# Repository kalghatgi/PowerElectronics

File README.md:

View this project on [CADLAB.io](https://cadlab.io/project/28492). 

# PowerElectronics

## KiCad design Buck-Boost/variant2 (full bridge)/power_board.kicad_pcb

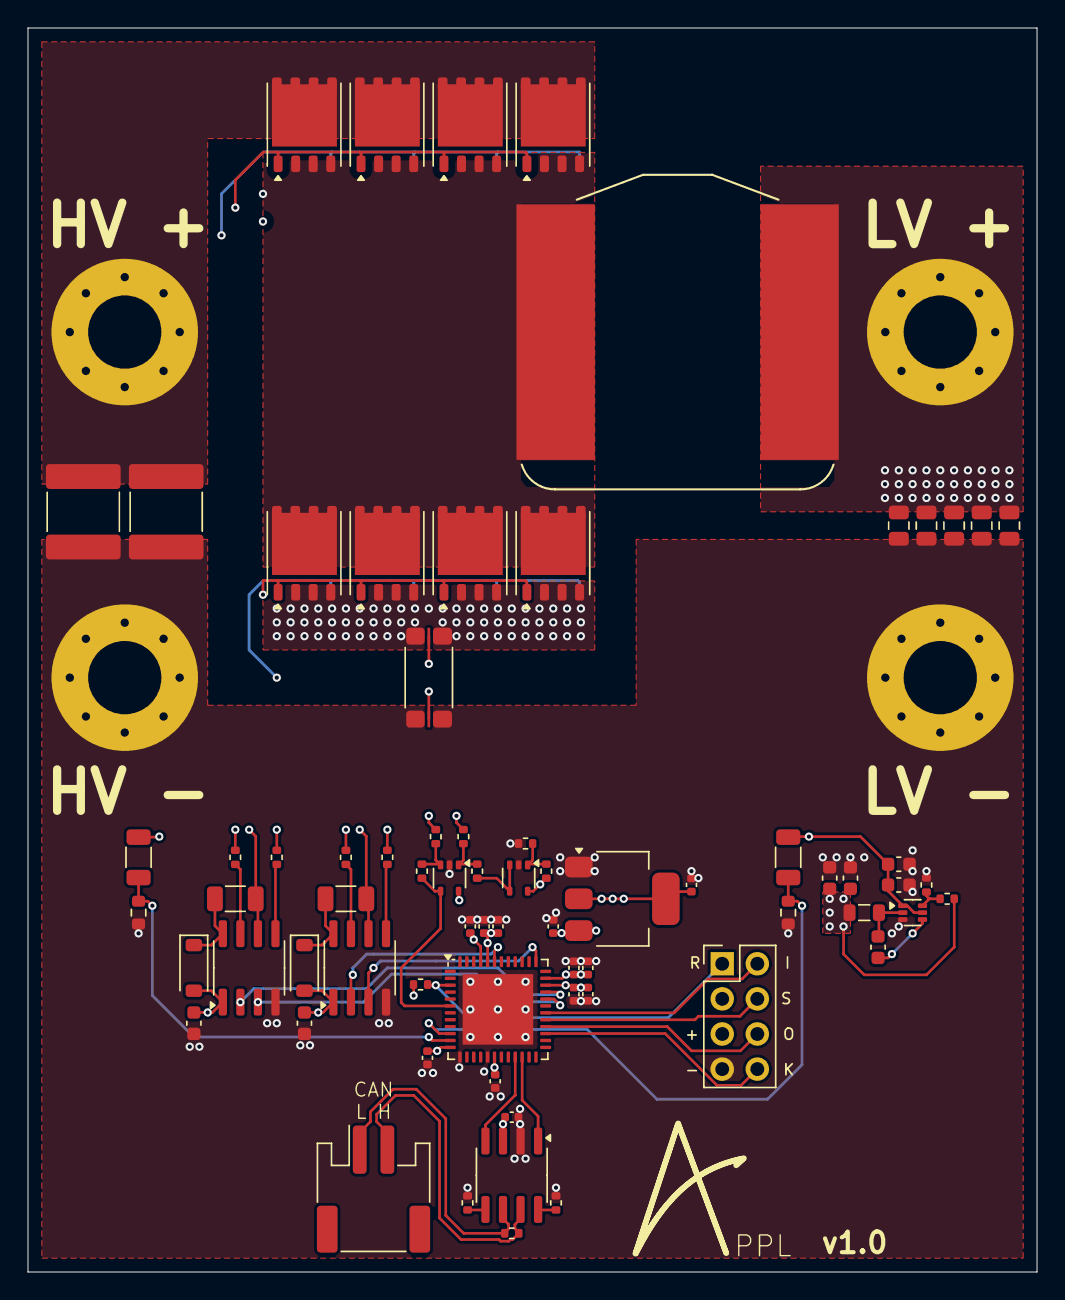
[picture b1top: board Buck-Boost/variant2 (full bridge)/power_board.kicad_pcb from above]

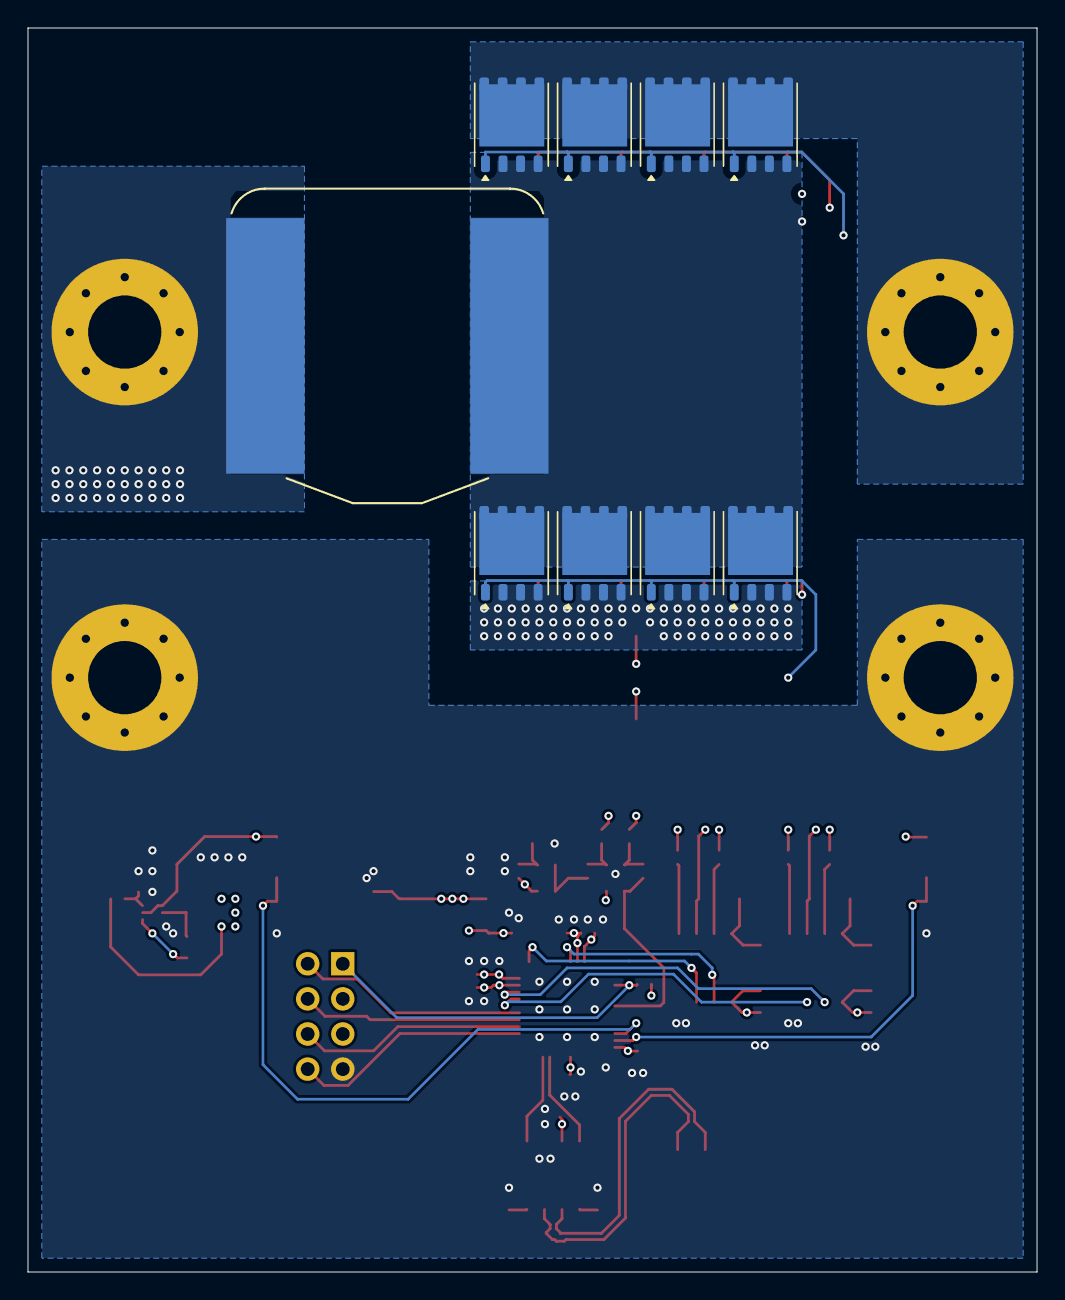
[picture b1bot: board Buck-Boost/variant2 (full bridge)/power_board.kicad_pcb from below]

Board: 4 copper layers, 73.0 x 90.0 mm, 84 parts (9 on the bottom side), 45 nets.

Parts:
C1, C2: 22uF, >=120V; C_2220_5750Metric
C3, C4, C5, C6, C7: >22uF, >25V; C_0805_2012Metric
C8, C31, C33: 10uF, >=25V; C_0603_1608Metric
C10, C13: 100nF, >=25V; C_0603_1608Metric
C12, C14, C26, C27, C28, C29, C30: 1uF, >=6.3V; C_0402_1005Metric
C18, C21: 22uF, >=6.3V; C_0603_1608Metric
C19, C25: 10uF, >=6.3V; C_0402_1005Metric
C22, C24: 100nF, >=6.3V; C_0402_1005Metric
C23: 4.7uF, >=6.3V; C_0402_1005Metric
C32, C34: 100nF, >=25V; C_1206_3216Metric
D3, D4: Vr>=600V, If>=1A; D_SOD-123
H1, H2, H3, H4: MountingHole_Pad; MountingHole_5.3mm_M5_Pad_Via
IC1: F2800137RGZR; QFN-48-1EP_7x7mm_P0.5mm_EP5.1x5.1mm
J1: Conn_01x02_Pin; JST_PH_S2B-PH-SM4-TB_1x02-1MP_P2.00mm_Horizontal
J3: Conn_02x04_Counter_Clockwise; PinHeader_2x04_P2.54mm_Vertical
L1, L2: 15uH, IRMS>100A, Isat>175A; IND_MPX1D2213L680_KEM
L4: 3.3uH, >=0.5A; L_0805_2012Metric
Q1, Q2, Q3, Q4, Q5, Q6, Q7, Q8, Q9, Q10, Q11, Q12, Q13, Q14, Q15, Q16: NMOS, Vds>=80V, Rds<=1.5mOhm; Infineon_PG-TDSON-8_6.15x5.15mm
R1, R4: 1MOhm, >200V, <1%, >62.5mW; R_1206_3216Metric
R2, R5: 10K, >62.5mW; R_0603_1608Metric
R3: 500uOhm, >=3W; R_shunt_2512_6332Metric
R6, R7, R8, R9, R13, R14, R17, R18, R27: 10K, 62.5mW, 0402; R_0402_1005Metric
R15, R16, R28, R29: 4R, 62.5mW, 0402; R_0402_1005Metric
R21: 120R, 62.5mW, 0402; R_0402_1005Metric
R22: 30.9K, >62.5mW, 0402; R_0402_1005Metric
R23: 10K, >62.5mW, 0402; R_0402_1005Metric
U1, U5: LMV321; SOT-353_SC-70-5
U2: TCAN3414DR; SOIC-8_3.9x4.9mm_P1.27mm
U3: TPS562202; SOT-563
U4: LD1117S12TR_SOT223; SOT-223-3_TabPin2
U6, U7: IR2101; SOIC-8_3.9x4.9mm_P1.27mm

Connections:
+1.2V: C19.1, C22.1, C23.1, C24.1, C25.1, IC1.35 (VDD), IC1.44 (VDD), U4.2 (VO)
+3.3V: C12.1, C14.1, C18.1, C21.1, C26.1, C27.1, C28.1, C29.1, C30.1, IC1.12 (VREFHI), IC1.18 (VDDA), IC1.34 (VDDIO), IC1.45 (VDDIO), J3.5, L4.1, R6.1, R22.1, R27.1, U1.5 (V+), U2.3 (VCC), U4.3 (VI), U5.5 (V+)
+12V: C3.1, C4.1, C5.1, C6.1, C7.1, C8.1, C10.1, C31.1, C33.1, D3.2 (A), D4.2 (A), H1.1, L1.1, L2.1, R4.1, U3.1 (VIN), U3.5 (EN), U6.1 (VCC), U7.1 (VCC)
/CAN_N: J1.1, R21.2, U2.6 (CANL)
/CAN_P: J1.2, R21.1, U2.7 (CANH)
/CAN_Rx: IC1.21 (A10/C10/GPIO230), U2.4 (RXD)
/CAN_Tx: IC1.22 (A19/C19/GPIO13), U2.1 (TXD)
/HG_A: Q9.1 (G), Q11.1 (G), Q13.1 (G), Q15.1 (G), R28.1
/HG_B: Q1.1 (G), Q3.1 (G), Q5.1 (G), Q7.1 (G), R15.1
/HS_A: C32.2, L1.2, Q9.2 (S), Q9.3 (S), Q9.4 (S), Q10.5 (D), Q11.2 (S), Q11.3 (S), Q11.4 (S), Q12.5 (D), Q13.2 (S), Q13.3 (S), Q13.4 (S), Q14.5 (D), Q15.2 (S), Q15.3 (S), Q15.4 (S), Q16.5 (D), U7.6 (VS)
/HS_B: C34.2, L2.2, Q1.2 (S), Q1.3 (S), Q1.4 (S), Q2.5 (D), Q3.2 (S), Q3.3 (S), Q3.4 (S), Q4.5 (D), Q5.2 (S), Q5.3 (S), Q5.4 (S), Q6.5 (D), Q7.2 (S), Q7.3 (S), Q7.4 (S), Q8.5 (D), U6.6 (VS)
/HV+: C1.1, C2.1, H4.1, Q1.5 (D), Q3.5 (D), Q5.5 (D), Q7.5 (D), Q9.5 (D), Q11.5 (D), Q13.5 (D), Q15.5 (D), R1.1
/I: IC1.6 (A2/C9/GPIO224), R18.1, U5.4
/I+: R3.3, R13.2
/I-: R3.2, R14.2
/LG_A: Q10.1 (G), Q12.1 (G), Q14.1 (G), Q16.1 (G), R29.1
/LG_B: Q2.1 (G), Q4.1 (G), Q6.1 (G), Q8.1 (G), R16.1
/PWM_H_A: IC1.43 (GPIO7), U7.2 (HIN)
/PWM_H_B: IC1.33 (GPIO19X1), U6.2 (HIN)
/PWM_L_A: IC1.37 (GPIO4), U7.3 (LIN)
/PWM_L_B: IC1.32 (GPIO18X2), U6.3 (LIN)
/TCK: IC1.27 (TCK), J3.8
/TDI: IC1.30 (GPIO35/TDI), J3.2
/TDO: IC1.28 (GPIO37/TDO), J3.6
/TMS: IC1.29 (TMS), J3.4
/V_hv: IC1.11 (A0/C15/CMP1_DACL), R1.2, R2.1
/V_lv: IC1.10 (A1), R4.2, R5.1
/~RST: IC1.3 (XRSN), J3.1, R27.2
GND0: C1.2, C2.2, C3.2, C4.2, C5.2, C6.2, C7.2, C8.2, C10.2, C12.2, C14.2, C18.2, C19.2, C21.2, C22.2, C23.2, C24.2, C25.2, C26.2, C27.2, C28.2, C29.2, C30.2, C31.2, C33.2, H2.1, H3.1, IC1.13 (VREFLO), IC1.17 (VSSA), IC1.49 (VSS), J3.7, R2.2, R3.4, R5.2, R7.2, R8.2, R9.2, R23.2, U1.2 (V-), U2.2 (GND), U3.3 (GND), U4.1 (GND), U5.2 (V-), U6.4 (COM), U7.4 (COM)
unnamed: C32.1, D3.1 (K), U7.8 (VB)
unnamed: C34.1, D4.1 (K), U6.8 (VB)
unnamed: Q2.2 (S), Q2.3 (S), Q2.4 (S), Q4.2 (S), Q4.3 (S), Q4.4 (S), Q6.2 (S), Q6.3 (S), Q6.4 (S), Q8.2 (S), Q8.3 (S), Q8.4 (S), Q10.2 (S), Q10.3 (S), Q10.4 (S), Q12.2 (S), Q12.3 (S), Q12.4 (S), Q14.2 (S), Q14.3 (S), Q14.4 (S), Q16.2 (S), Q16.3 (S), Q16.4 (S), R3.1
unnamed: R6.2, R7.1, U1.1 (+)
unnamed: R17.2, U1.3 (-), U1.4
unnamed: R8.1, U2.5 (SHDN)
unnamed: R9.1, U2.8 (STB)
unnamed: C13.1, L4.2, U3.2 (SW)
unnamed: C13.2, U3.4 (VBST)
unnamed: R22.2, R23.1, U3.6 (VFB)
unnamed: R13.1, R17.1, U5.1 (+)
unnamed: R14.1, R18.2, U5.3 (-)
unnamed: R15.2, U6.7 (HO)
unnamed: R16.2, U6.5 (LO)
unnamed: R28.2, U7.7 (HO)
unnamed: R29.2, U7.5 (LO)

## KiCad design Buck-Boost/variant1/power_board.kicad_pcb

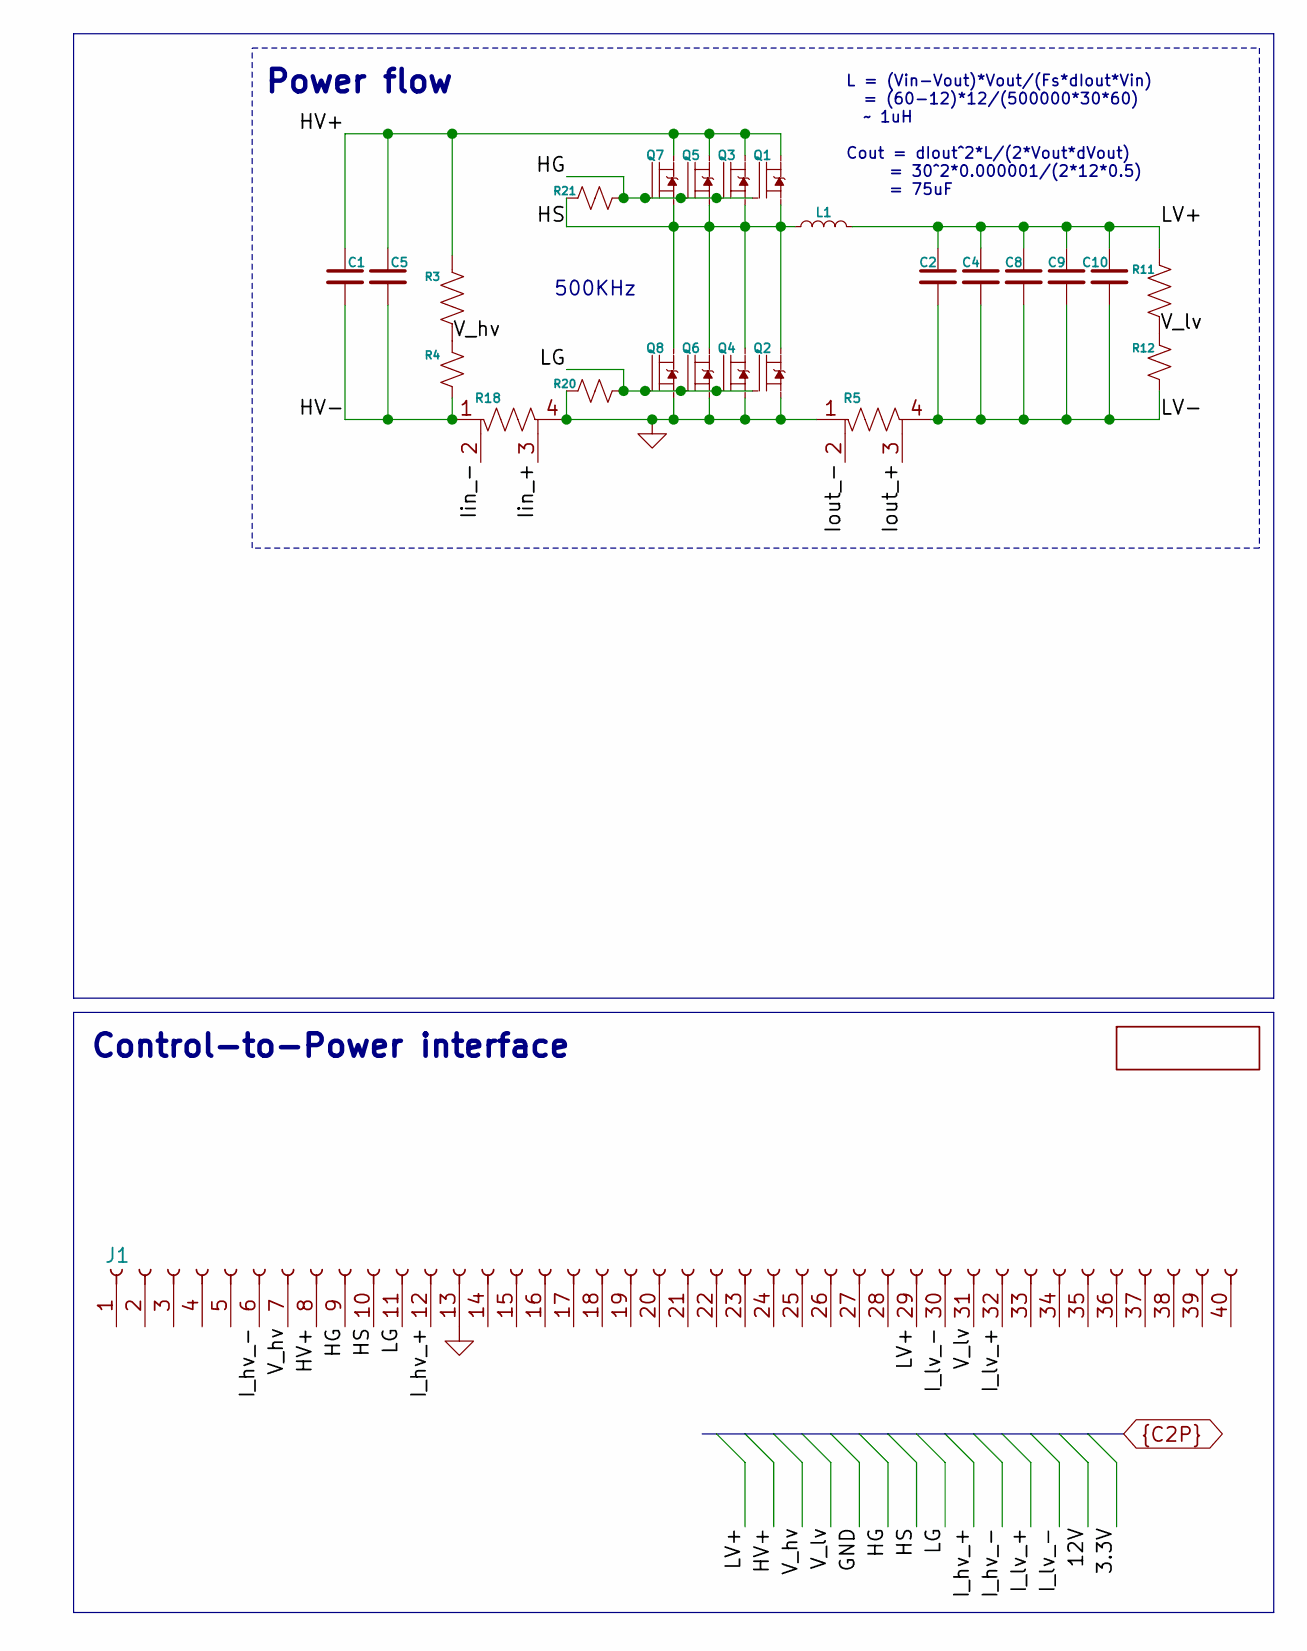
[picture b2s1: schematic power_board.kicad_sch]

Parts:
C1, C5: 22uF, >=120V; C_2220_5750Metric
C2, C4, C8, C9, C10: >22uF, >25V; C_0805_2012Metric
J1: Conn_01x05_Header; PinHeader_1x40_P2.54mm_Vertical_SMD_Pin1Left
L1: 15uH, IRMS>100A, Isat>175A; IND_MPX1D2213L680_KEM; MPN MPX1D2213L1R0
Q1, Q2, Q3, Q4, Q5, Q6, Q7, Q8: NMOS, Vds>=80V, Rds<=1.5mOhm; Infineon_PG-TDSON-8_6.15x5.15mm; MPN IAUCN04S7N005ATMA1
R3, R11: 1MOhm, >200V, <1%, >62.5mW; R_1206_3216Metric
R4, R12: 10K, >62.5mW; R_0603_1608Metric
R5, R18: 500uOhm, >=3W; R_shunt_2512_6332Metric
R20, R21: 10K, >62.5mW, 0402; R_0402_1005Metric

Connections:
/HV-: C1.2, C5.2, R4.2, R18.1
/Iin_+: R18.3
/Iin_-: R18.2
/Iout_+: R5.3
/Iout_-: R5.2
/LV-: C2.2, C4.2, C8.2, C9.2, C10.2, R5.4, R12.2
GND0: J1.13, Q2.2 (S), Q2.3 (S), Q2.4 (S), Q4.2 (S), Q4.3 (S), Q4.4 (S), Q6.2 (S), Q6.3 (S), Q6.4 (S), Q8.2 (S), Q8.3 (S), Q8.4 (S), R5.1, R18.4, R20.2
HG: J1.9, Q1.1 (G), Q3.1 (G), Q5.1 (G), Q7.1 (G), R21.1
HS: J1.10, L1.2, Q1.2 (S), Q1.3 (S), Q1.4 (S), Q2.5 (D), Q3.2 (S), Q3.3 (S), Q3.4 (S), Q4.5 (D), Q5.2 (S), Q5.3 (S), Q5.4 (S), Q6.5 (D), Q7.2 (S), Q7.3 (S), Q7.4 (S), Q8.5 (D), R21.2
HV+: C1.1, C5.1, J1.8, Q1.5 (D), Q3.5 (D), Q5.5 (D), Q7.5 (D), R3.1
I_hv_+: J1.12
I_hv_-: J1.6
I_lv_+: J1.32
I_lv_-: J1.30
LG: J1.11, Q2.1 (G), Q4.1 (G), Q6.1 (G), Q8.1 (G), R20.1
LV+: C2.1, C4.1, C8.1, C9.1, C10.1, J1.29, L1.1, R11.1
V_hv: J1.7, R3.2, R4.1
V_lv: J1.31, R11.2, R12.1

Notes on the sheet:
500KHz
Power flow
Control-to-Power interface
L = (Vin-Vout)*Vout/(Fs*dIout*Vin) = (60-12)*12/(500000*30*60) ~ 1uH Cout = dIout^2*L/(2*Vout*dVout) = 30^2*0.000001/(2*12*0.5) = 75uF

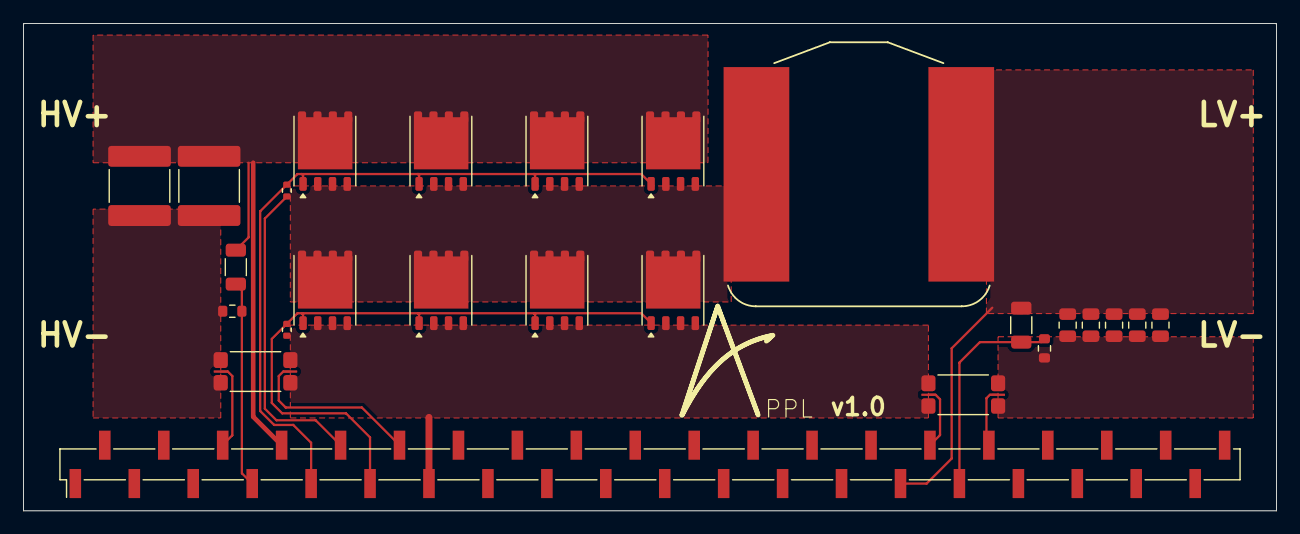
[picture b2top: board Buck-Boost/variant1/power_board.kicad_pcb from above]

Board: 2 copper layers, 108.0 x 42.0 mm, 25 parts (0 on the bottom side), 10 nets.

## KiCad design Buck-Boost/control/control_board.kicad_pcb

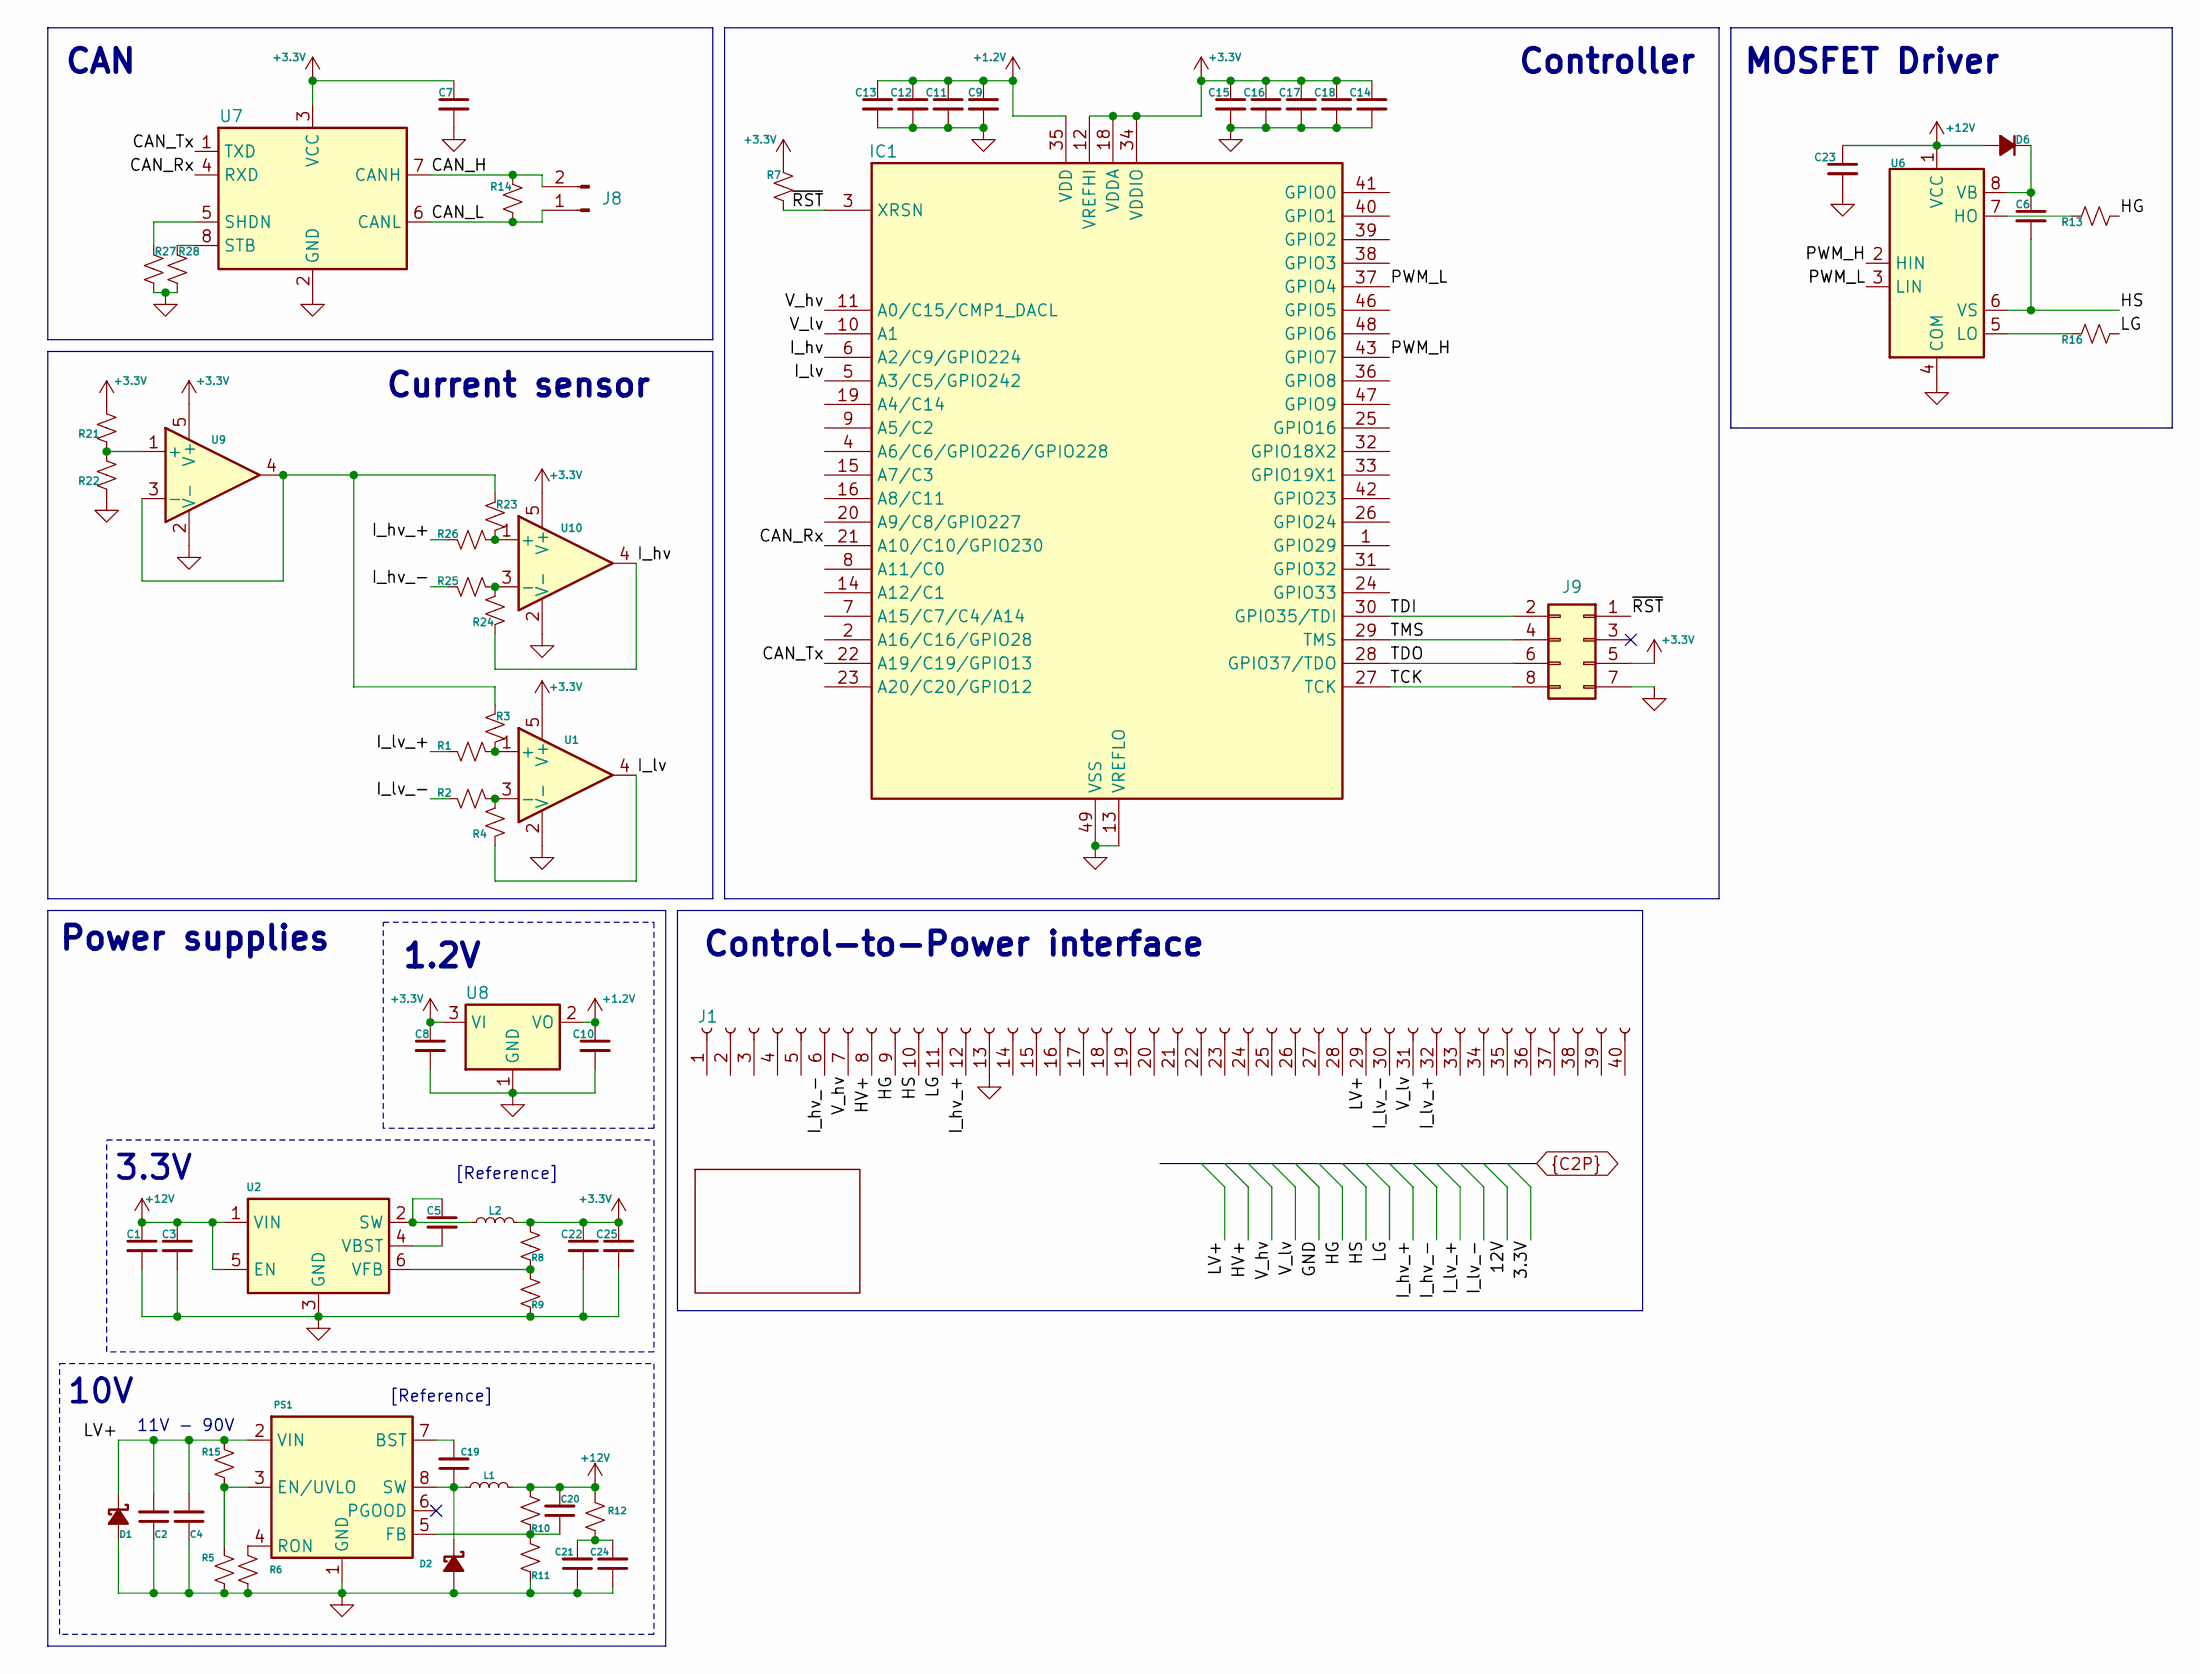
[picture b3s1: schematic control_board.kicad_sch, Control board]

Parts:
C1, C23: 10uF, >=25V; C_0603_1608Metric
C2, C4: 2.2uF, >=100V, 1206; C_1210_3225Metric; MPN mcmt32b225k101ct
C3, C5: 100nF, >=25V; C_0603_1608Metric
C6: 100nF, >=25V; C_1206_3216Metric
C7, C8, C14, C15, C16, C17, C18: 1uF, >=6.3V; C_0402_1005Metric
C9, C10: 10uF, >=6.3V; C_0402_1005Metric
C11, C13: 100nF, >=6.3V; C_0402_1005Metric
C12: 4.7uF, >=6.3V; C_0402_1005Metric
C19: 2200pF, >=25V, 0603; C_0603_1608Metric; MPN mc0805b222k500ct
C20: 100pF, >=25V, 0402; C_0402_1005Metric; MPN mc0402b101k500ct
C21, C24: 22uF, >=25V, 0603; C_0603_1608Metric; MPN grm21br61e226me44k
C22, C25: 22uF, >=6.3V; C_0603_1608Metric
D1: Vs=110V Vb=120V SOD-123; D_SOD-123F; MPN pmeg120g10elrx
D2: Vr=100V Vf=0.6V If=2.5A; D_SMP_DO-220AA; MPN v3pm10-m3-h
D6: Vr>=600V, If>=1A; D_SOD-123
IC1: F2800137RGZR; QFN-48-1EP_7x7mm_P0.5mm_EP5.1x5.1mm
J1: Conn_01x05_Header; PinSocket_1x40_P2.54mm_Horizontal
J8: Conn_01x02_Pin; JST_PH_S2B-PH-SM4-TB_1x02-1MP_P2.00mm_Horizontal
J9: Conn_02x04_Counter_Clockwise; PinHeader_2x04_P2.54mm_Vertical
L1: 150uH, <=900mOhm; L_Taiyo-Yuden_MD-4040; MPN 74404054151
L2: 3.3uH, >=0.5A; L_0805_2012Metric; MPN LQM21PN3R3NGRD
PS1: Vin>=90V, Iout>=2.0A; SOIC-8-1EP_3.9x4.9mm_P1.27mm_EP2.29x3mm_ThermalVias; MPN LM5012DDAR
R1, R2, R3, R4, R7, R21, R22, R23, R24, R25, R26, R27, R28: 10K, 62.5mW, 0402; R_0402_1005Metric
R5: 16.9K, >=62.5mW, 0402; R_0402_1005Metric
R6: 59K, >=62.5mW, 0402; R_0402_1005Metric; MPN mcwr04x5902ftl
R8: 30.9K, >62.5mW, 0402; R_0402_1005Metric
R9: 10K, >62.5mW, 0402; R_0402_1005Metric
R10: 732K, >=62.5mW, 0402; R_0402_1005Metric
R11: 101K, >=62.5mW, 0402; R_0402_1005Metric
R12: 0.560R, 62.5mW, 0402; R_0402_1005Metric; MPN rl0402fr-070r5l
R13, R16: 4R, 62.5mW, 0402; R_0402_1005Metric
R14: 120R, 62.5mW, 0402; R_0402_1005Metric
R15: 100K, >=62.5mW, 0402; R_0805_2012Metric
U1, U9, U10: LMV321; SOT-353_SC-70-5
U2: TPS562202; SOT-563
U6: IR2101; SOIC-8_3.9x4.9mm_P1.27mm
U7: TCAN3414DR; SOIC-8_3.9x4.9mm_P1.27mm
U8: LD1117S12TR_SOT223; SOT-223-3_TabPin2

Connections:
+1.2V: C9.1, C10.1, C11.1, C12.1, C13.1, IC1.35 (VDD), IC1.44 (VDD), U8.2 (VO)
+3.3V: C7.1, C8.1, C14.1, C15.1, C16.1, C17.1, C18.1, C22.1, C25.1, IC1.12 (VREFHI), IC1.18 (VDDA), IC1.34 (VDDIO), IC1.45 (VDDIO), J9.5, L2.1, R7.1, R8.1, R21.1, U1.5 (V+), U7.3 (VCC), U8.3 (VI), U9.5 (V+), U10.5 (V+)
+12V: C1.1, C3.1, C20.2, C23.1, D6.2 (A), L1.2, R10.1, R12.1, U2.1 (VIN), U2.5 (EN), U6.1 (VCC)
/CAN_H: J8.2, R14.1, U7.7 (CANH)
/CAN_L: J8.1, R14.2, U7.6 (CANL)
/CAN_Rx: IC1.21 (A10/C10/GPIO230), U7.4 (RXD)
/CAN_Tx: IC1.22 (A19/C19/GPIO13), U7.1 (TXD)
/I_hv: IC1.6 (A2/C9/GPIO224), R24.1, U10.4
/I_lv: IC1.5 (A3/C5/GPIO242), R4.1, U1.4
/PWM_H: IC1.43 (GPIO7), U6.2 (HIN)
/PWM_L: IC1.37 (GPIO4), U6.3 (LIN)
/TCK: IC1.27 (TCK), J9.8
/TDI: IC1.30 (GPIO35/TDI), J9.2
/TDO: IC1.28 (GPIO37/TDO), J9.6
/TMS: IC1.29 (TMS), J9.4
/~RST: IC1.3 (XRSN), J9.1, R7.2
GND0: C1.2, C2.1, C3.2, C4.1, C7.2, C8.2, C9.2, C10.2, C11.2, C12.2, C13.2, C14.2, C15.2, C16.2, C17.2, C18.2, C21.1, C22.2, C23.2, C24.1, C25.2, D1.2 (A), D2.2 (A), IC1.13 (VREFLO), IC1.17 (VSSA), IC1.49 (VSS), J1.13, J9.7, PS1.1 (GND), PS1.9 (GND_thermal), R5.2, R6.1, R9.2, R11.2, R22.2, R27.2, R28.2, U1.2 (V-), U2.3 (GND), U6.4 (COM), U7.2 (GND), U8.1 (GND), U9.2 (V-), U10.2 (V-)
HG: J1.9, R13.1
HS: C6.2, J1.10, U6.6 (VS)
HV+: J1.8
I_hv_+: J1.12, R26.2
I_hv_-: J1.6, R25.2
I_lv_+: J1.32, R1.2
I_lv_-: J1.30, R2.2
LG: J1.11, R16.1
LV+: C2.2, C4.2, D1.1 (K), J1.29, PS1.2 (VIN), R15.1
unnamed: C21.2, C24.2, R12.2
unnamed: C19.1, D2.1 (K), L1.1, PS1.8 (SW)
unnamed: C6.1, D6.1 (K), U6.8 (VB)
unnamed: C19.2, PS1.7 (BST)
unnamed: PS1.3 (EN/UVLO), R5.1, R15.2
unnamed: C20.1, PS1.5 (FB), R10.2, R11.1
unnamed: PS1.4 (RON), R6.2
unnamed: R1.1, R3.1, U1.1 (+)
unnamed: R2.1, R4.2, U1.3 (-)
unnamed: C5.1, L2.2, U2.2 (SW)
unnamed: C5.2, U2.4 (VBST)
unnamed: R8.2, R9.1, U2.6 (VFB)
unnamed: R13.2, U6.7 (HO)
unnamed: R16.2, U6.5 (LO)
unnamed: R27.1, U7.5 (SHDN)
unnamed: R28.1, U7.8 (STB)
unnamed: R21.2, R22.1, U9.1 (+)
unnamed: R3.2, R23.2, U9.3 (-), U9.4
unnamed: R23.1, R26.1, U10.1 (+)
unnamed: R24.2, R25.1, U10.3 (-)
V_hv: IC1.11 (A0/C15/CMP1_DACL), J1.7
V_lv: IC1.10 (A1), J1.31

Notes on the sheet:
11V - 90V
[Reference]
Control-to-Power interface
10V
Controller
MOSFET Driver
CAN
1.2V
Power supplies
3.3V
Current sensor

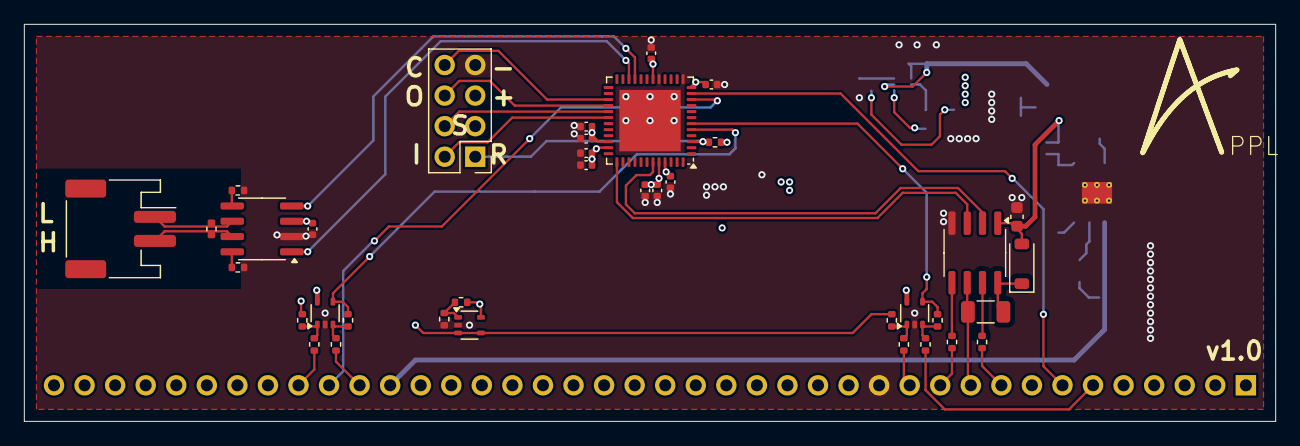
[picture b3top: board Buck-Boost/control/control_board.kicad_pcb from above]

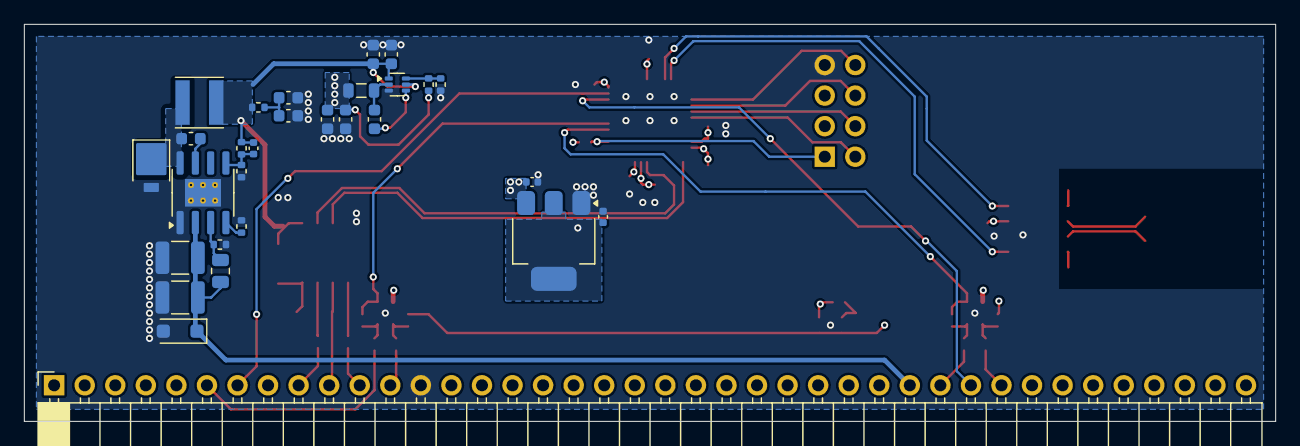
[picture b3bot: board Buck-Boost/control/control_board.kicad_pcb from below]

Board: 4 copper layers, 104.0 x 33.0 mm, 66 parts (29 on the bottom side), 47 nets.

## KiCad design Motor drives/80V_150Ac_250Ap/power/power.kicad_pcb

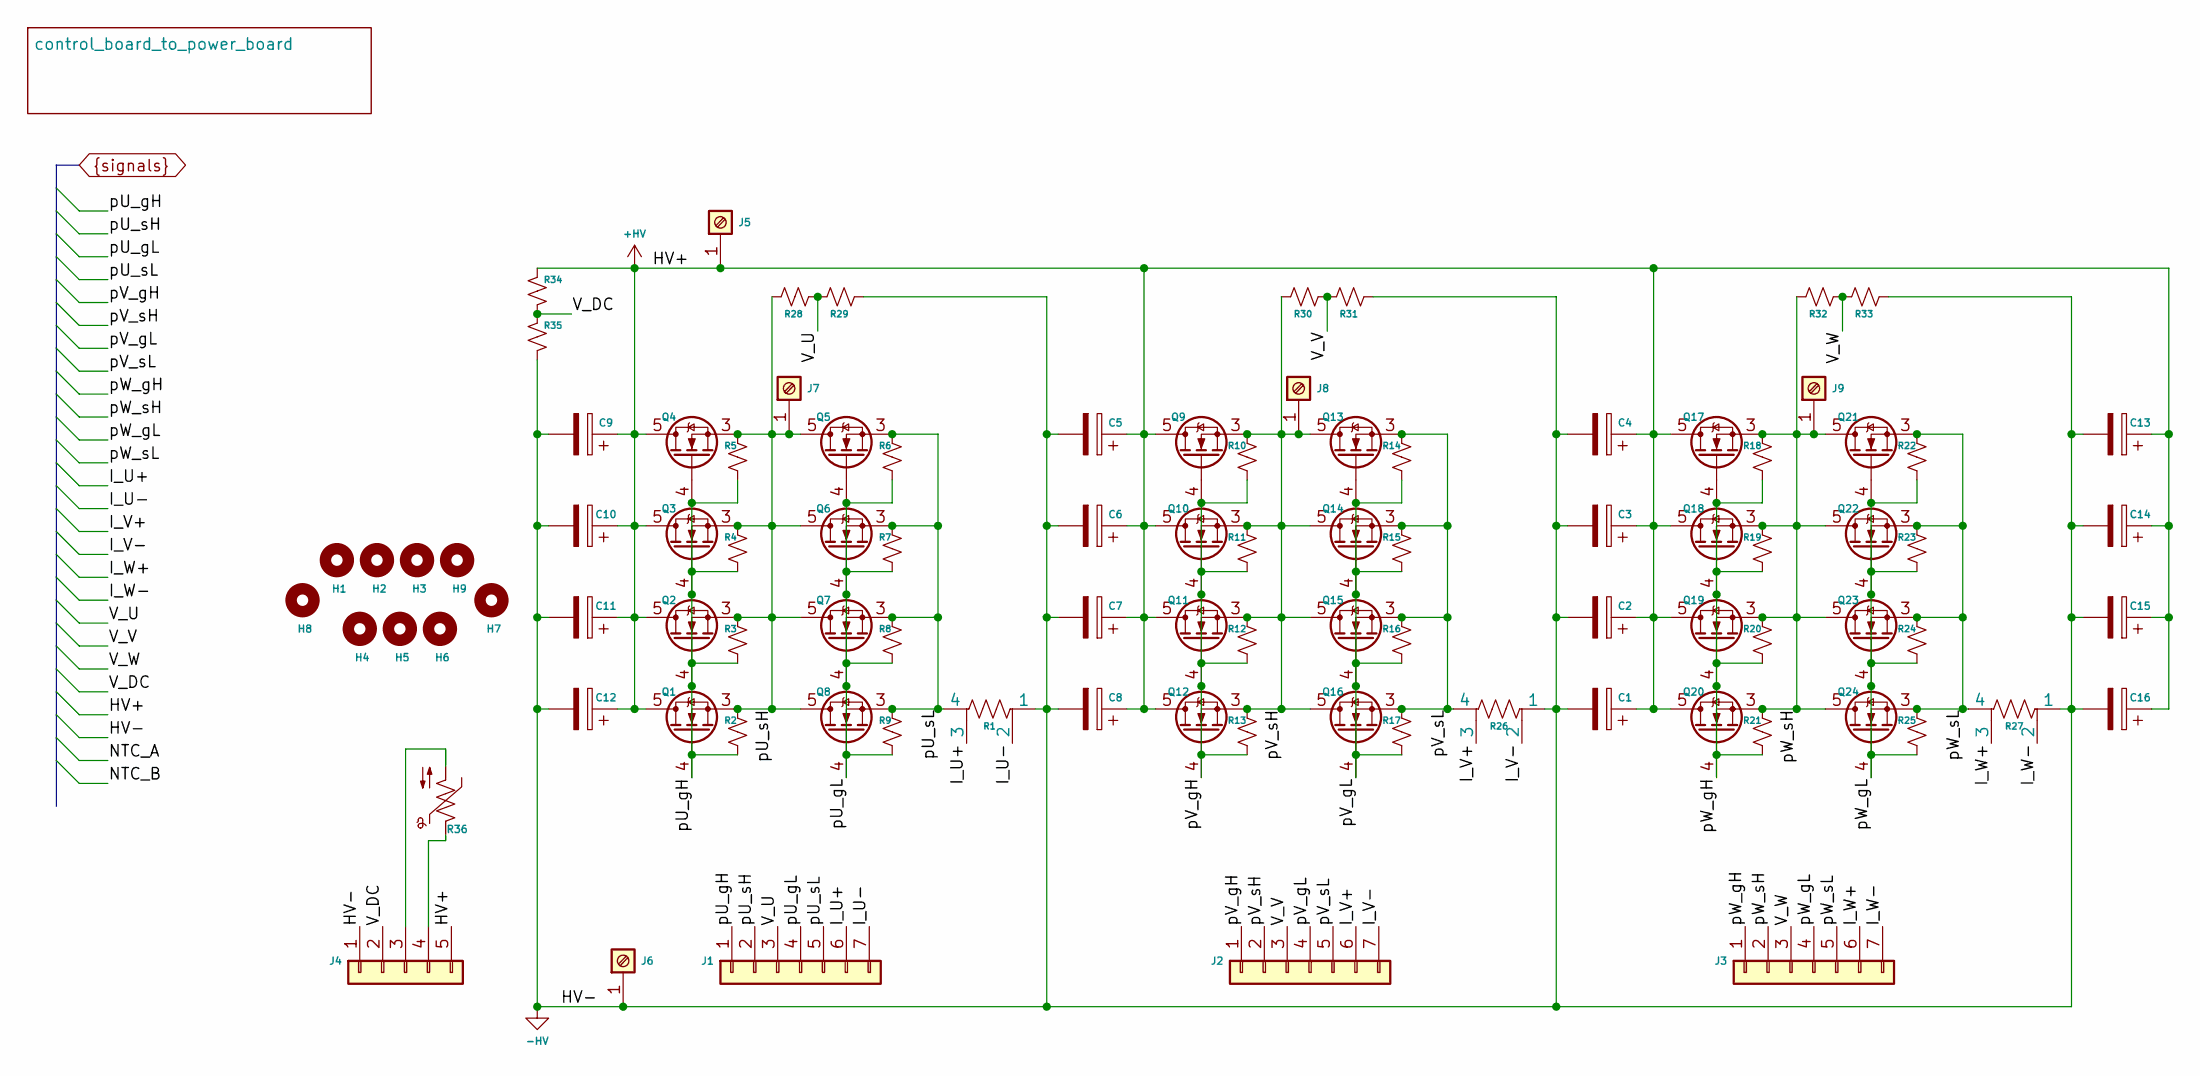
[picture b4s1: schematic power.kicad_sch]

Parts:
C1, C2, C3, C4, C5, C6, C7, C8, C9, C10, C11, C12, C13, C14, C15, C16: 220uF, >=120V; CP_Elec_18x17.5
H1, H2, H3, H4, H5, H6, H7, H8, H9: M3, no pads; M3 x 6mm brass threaded hex spacer
J1, J2, J3: Conn_01x07; PinSocket_1x07_P2.54mm_Vertical_SMD_Pin1Left
J4: Conn_01x05; PinSocket_1x05_P2.54mm_Vertical_SMD_Pin1Left
J5, J6, J7, J8, J9: M8 lug; terminal_lug
Q1, Q2, Q3, Q4, Q5, Q6, Q7, Q8, Q9, Q10, Q11, Q12, Q13, Q14, Q15, Q16, Q17, Q18, Q19, Q20, Q21, Q22, Q23, Q24: NMOS, >80V, <1.5mOhm; IAUCN08S7N013ATMA1; MPN IAUCN08S7N013ATMA1
R1, R26, R27: 100uOhms, 15W; RES_Y14860R00010F9R_VIS_1; MPN Y14860R00010F9R
R2, R3, R4, R5, R6, R7, R8, R9, R10, R11, R12, R13, R14, R15, R16, R17, R18, R19, R20, R21, R22, R23, R24, R25, R29, R31, R33, R35: 10K, >=62.5mW, 0402; R_0402_1005Metric; MPN mcwr04x1002ftl
R28, R30, R32, R34: 220K, >=62.5mW, 0805; R_0805_2012Metric
R36: 10K NTC; R_0603_1608Metric; MPN tx06f103f3435er

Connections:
+HV: C1.1, C2.1, C3.1, C4.1, C5.1, C6.1, C7.1, C8.1, C9.1, C10.1, C11.1, C12.1, C13.1, C14.1, C15.1, C16.1, J4.5, J5.1, Q1.5 (D), Q2.5 (D), Q3.5 (D), Q4.5 (D), Q9.5 (D), Q10.5 (D), Q11.5 (D), Q12.5 (D), Q17.5 (D), Q18.5 (D), Q19.5 (D), Q20.5 (D), R34.2
-HV: C1.2, C2.2, C3.2, C4.2, C5.2, C6.2, C7.2, C8.2, C9.2, C10.2, C11.2, C12.2, C13.2, C14.2, C15.2, C16.2, J4.1, J6.1, R1.1, R26.1, R27.1, R29.1, R31.1, R33.1, R35.1
I_U+: J1.6, R1.3
I_U-: J1.7, R1.2
I_V+: J2.6, R26.3
I_V-: J2.7, R26.2
I_W+: J3.6, R27.3
I_W-: J3.7, R27.2
unnamed: J4.3, R36.2
unnamed: J4.4, R36.1
V_DC: J4.2, R34.1, R35.2
V_U: J1.3, R28.1, R29.2
V_V: J2.3, R30.1, R31.2
V_W: J3.3, R32.1, R33.2
pU_gH: J1.1, Q1.4 (G), Q2.4 (G), Q3.4 (G), Q4.4 (G), R2.1, R3.1, R4.1, R5.1
pU_gL: J1.4, Q5.4 (G), Q6.4 (G), Q7.4 (G), Q8.4 (G), R6.1, R7.1, R8.1, R9.1
pU_sH: J1.2, J7.1, Q1.1 (S), Q1.2 (S), Q1.3 (S), Q2.1 (S), Q2.2 (S), Q2.3 (S), Q3.1 (S), Q3.2 (S), Q3.3 (S), Q4.1 (S), Q4.2 (S), Q4.3 (S), Q5.5 (D), Q6.5 (D), Q7.5 (D), Q8.5 (D), R2.2, R3.2, R4.2, R5.2, R28.2
pU_sL: J1.5, Q5.1 (S), Q5.2 (S), Q5.3 (S), Q6.1 (S), Q6.2 (S), Q6.3 (S), Q7.1 (S), Q7.2 (S), Q7.3 (S), Q8.1 (S), Q8.2 (S), Q8.3 (S), R1.4, R6.2, R7.2, R8.2, R9.2
pV_gH: J2.1, Q9.4 (G), Q10.4 (G), Q11.4 (G), Q12.4 (G), R10.1, R11.1, R12.1, R13.1
pV_gL: J2.4, Q13.4 (G), Q14.4 (G), Q15.4 (G), Q16.4 (G), R14.1, R15.1, R16.1, R17.1
pV_sH: J2.2, J8.1, Q9.1 (S), Q9.2 (S), Q9.3 (S), Q10.1 (S), Q10.2 (S), Q10.3 (S), Q11.1 (S), Q11.2 (S), Q11.3 (S), Q12.1 (S), Q12.2 (S), Q12.3 (S), Q13.5 (D), Q14.5 (D), Q15.5 (D), Q16.5 (D), R10.2, R11.2, R12.2, R13.2, R30.2
pV_sL: J2.5, Q13.1 (S), Q13.2 (S), Q13.3 (S), Q14.1 (S), Q14.2 (S), Q14.3 (S), Q15.1 (S), Q15.2 (S), Q15.3 (S), Q16.1 (S), Q16.2 (S), Q16.3 (S), R14.2, R15.2, R16.2, R17.2, R26.4
pW_gH: J3.1, Q17.4 (G), Q18.4 (G), Q19.4 (G), Q20.4 (G), R18.1, R19.1, R20.1, R21.1
pW_gL: J3.4, Q21.4 (G), Q22.4 (G), Q23.4 (G), Q24.4 (G), R22.1, R23.1, R24.1, R25.1
pW_sH: J3.2, J9.1, Q17.1 (S), Q17.2 (S), Q17.3 (S), Q18.1 (S), Q18.2 (S), Q18.3 (S), Q19.1 (S), Q19.2 (S), Q19.3 (S), Q20.1 (S), Q20.2 (S), Q20.3 (S), Q21.5 (D), Q22.5 (D), Q23.5 (D), Q24.5 (D), R18.2, R19.2, R20.2, R21.2, R32.2
pW_sL: J3.5, Q21.1 (S), Q21.2 (S), Q21.3 (S), Q22.1 (S), Q22.2 (S), Q22.3 (S), Q23.1 (S), Q23.2 (S), Q23.3 (S), Q24.1 (S), Q24.2 (S), Q24.3 (S), R22.2, R23.2, R24.2, R25.2, R27.4

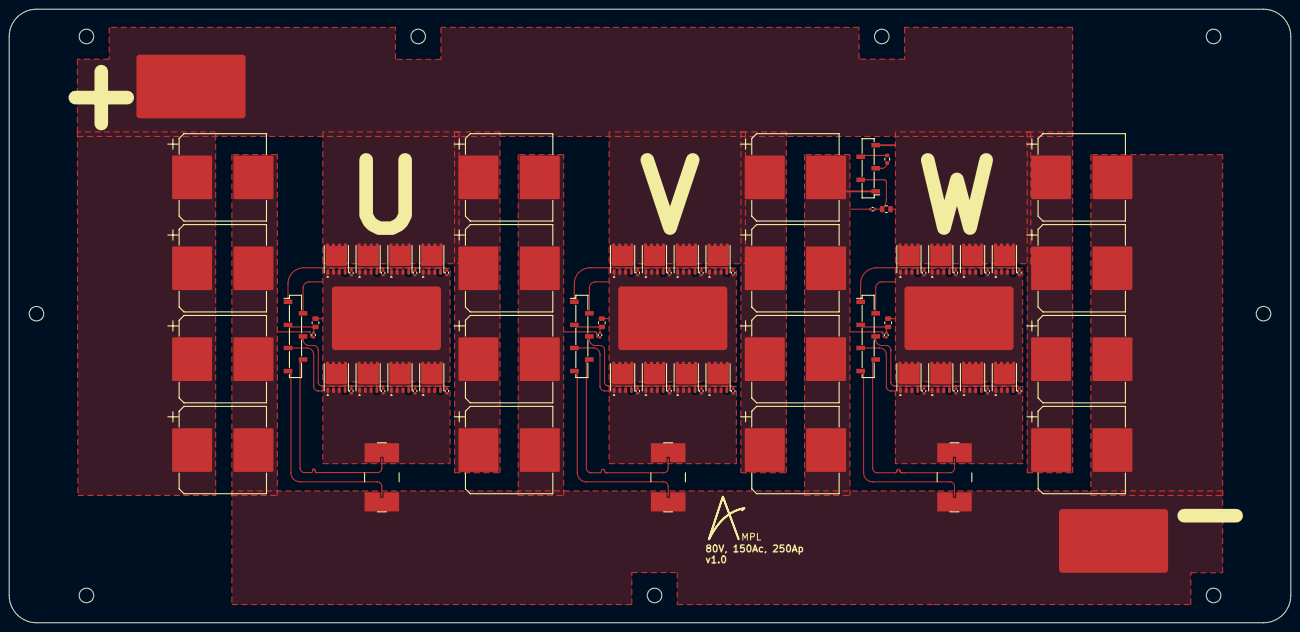
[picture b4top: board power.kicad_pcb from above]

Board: 2 copper layers, 282.0 x 135.0 mm, 94 parts (0 on the bottom side), 26 nets.
